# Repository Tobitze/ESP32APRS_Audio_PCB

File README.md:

This is a PCB for my APRS BLE TNC, which is based on the ESP32APRS_Audio Firmware from nakhonthai - see https://github.com/nakhonthai/ESP32APRS_Audio.
This PCB implements the basic components to work with an esp32s3 and an external handheld Radio, like filters and DC Offsets. The Radio is connected via the Kenwood Plug. This is not intended for an RF Module on the Board!
It's oriented around Nakhonthai's layouts with some small changes.
I designed it for my esp32s3-N16R8 (the one already on a PCB, not the chip itself). Please check your Pin configuration before using this.

TODO: This PCB has three UART Connectors, but no I2C für WX Sensors. You can reconfigure one of them, but the pin Layout then needs one wire on the pcb.

This PCB has:

-NPN transistor for PTT control

-GPIO PWM Filters (Audio Output)

-ADC Input DC Bias (Audio Input)

-UART Connectors for external GPS PCBs and other stuff (Supposed to be under the Board)

-Connectors for simple three-pin Sensors

-Every other Pin of the esp32 is led out to some connectors for future extensions, including four power pins

If you don't want to order this for yourself, get in touch; maybe I still have some lying around. (See qrz.com for email address)

73 de
DC4TA

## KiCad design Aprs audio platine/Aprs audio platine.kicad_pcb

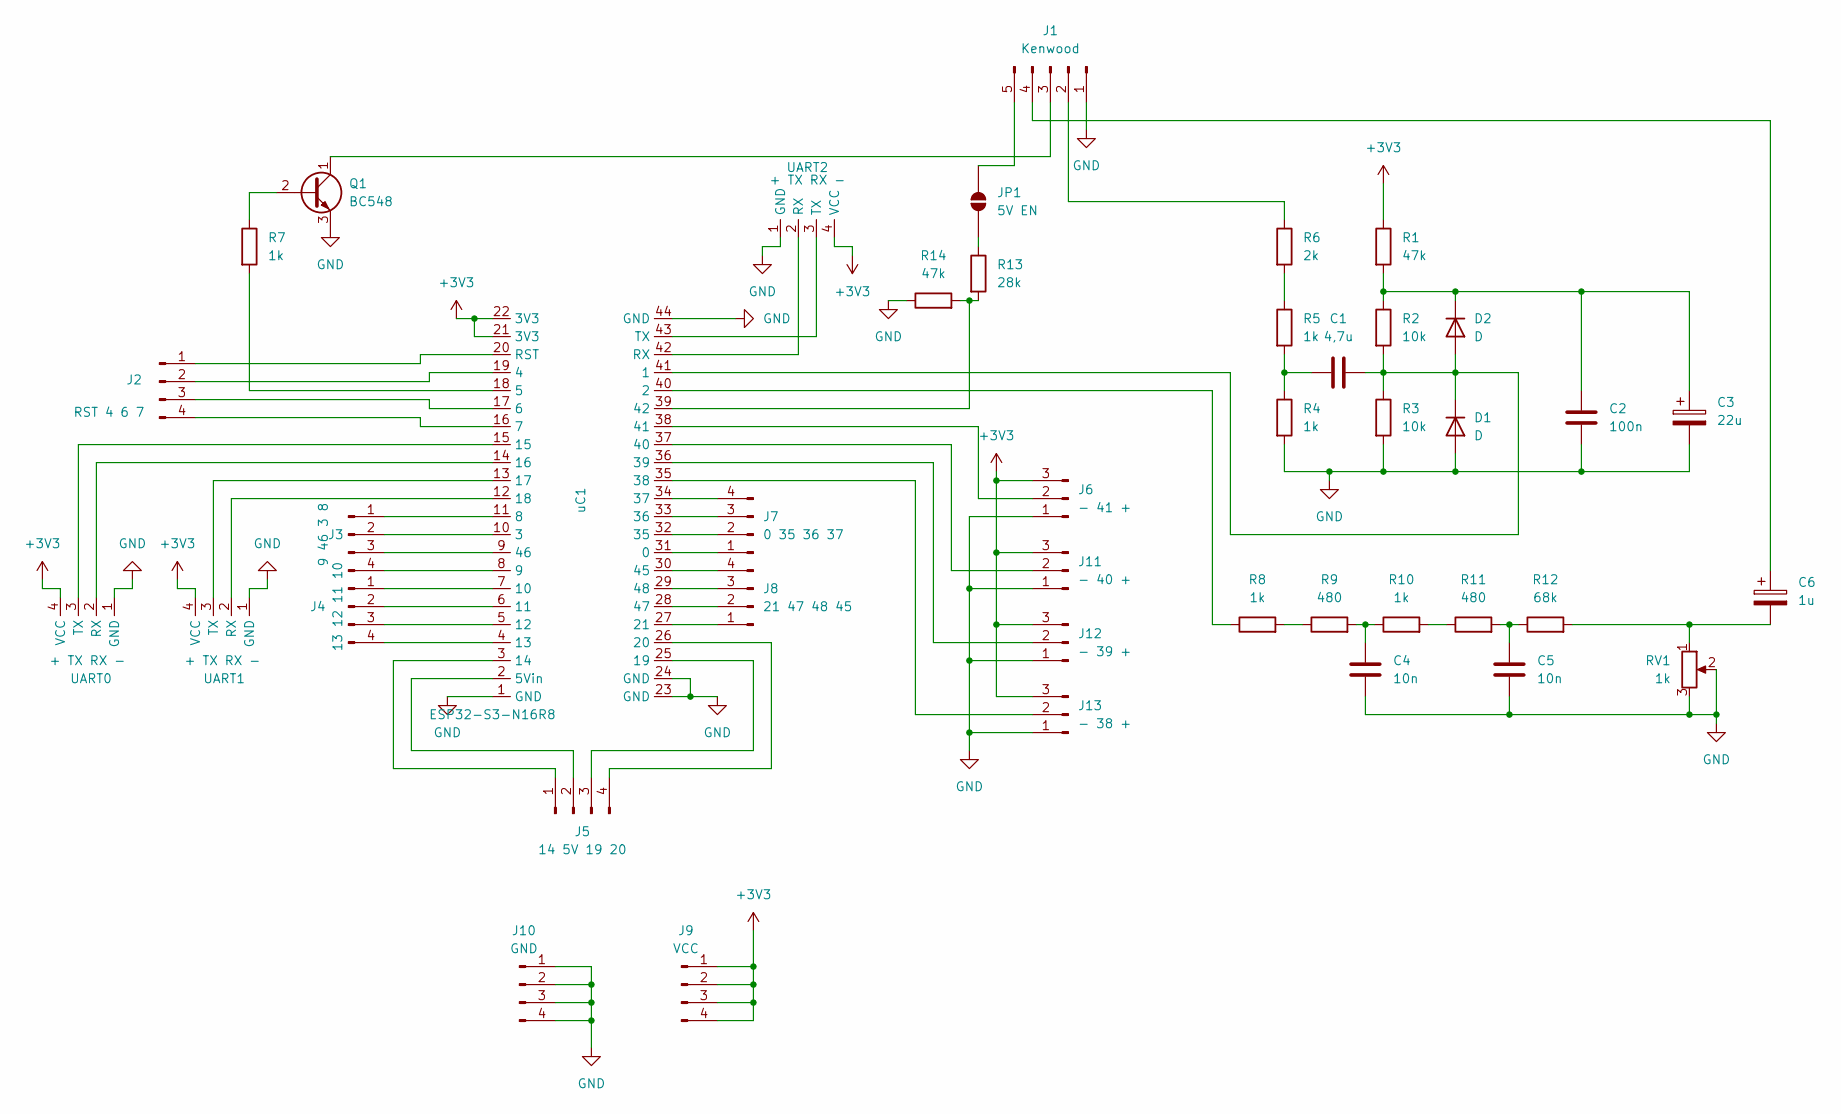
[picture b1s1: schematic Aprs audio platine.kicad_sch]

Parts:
C1: 4,7u; C_Disc_D3.0mm_W2.0mm_P2.50mm
C2: 100n; C_Disc_D3.0mm_W2.0mm_P2.50mm
C3: 22u; CP_Radial_D5.0mm_P2.50mm
C4, C5: 10n; C_Disc_D3.0mm_W2.0mm_P2.50mm
C6: 1u; CP_Radial_D5.0mm_P2.50mm
D1, D2: D; D_DO-34_SOD68_P7.62mm_Horizontal
J1: Kenwood; SolderWire-0.25sqmm_1x05_P4.2mm_D0.65mm_OD1.7mm
J2: RST 4 6 7; PinHeader_1x04_P2.54mm_Vertical
J3: 9 46 3 8; PinHeader_1x04_P2.54mm_Vertical
J4: 13 12 11 10; PinHeader_1x04_P2.54mm_Vertical
J5: 14 5V 19 20; PinHeader_1x04_P2.54mm_Vertical
J6: - 41 +; PinHeader_1x03_P2.54mm_Vertical
J7: 0 35 36 37; PinHeader_1x04_P2.54mm_Vertical
J8: 21 47 48 45; PinHeader_1x04_P2.54mm_Vertical
J9: VCC; PinHeader_1x04_P2.54mm_Vertical
J10: GND; PinHeader_1x04_P2.54mm_Vertical
J11: - 40 +; PinHeader_1x03_P2.54mm_Vertical
J12: - 39 +; PinHeader_1x03_P2.54mm_Vertical
J13: - 38 +; PinHeader_1x03_P2.54mm_Vertical
JP1: 5V EN; SolderJumper-2_P1.3mm_Open_RoundedPad1.0x1.5mm
Q1: BC548; TO-92_Inline
R1, R14: 47k; R_Axial_DIN0309_L9.0mm_D3.2mm_P12.70mm_Horizontal
R2, R3: 10k; R_Axial_DIN0309_L9.0mm_D3.2mm_P12.70mm_Horizontal
R4, R5, R7, R8, R10: 1k; R_Axial_DIN0309_L9.0mm_D3.2mm_P12.70mm_Horizontal
R6: 2k; R_Axial_DIN0309_L9.0mm_D3.2mm_P12.70mm_Horizontal
R9, R11: 480; R_Axial_DIN0309_L9.0mm_D3.2mm_P12.70mm_Horizontal
R12: 68k; R_Axial_DIN0309_L9.0mm_D3.2mm_P12.70mm_Horizontal
R13: 28k; R_Axial_DIN0309_L9.0mm_D3.2mm_P12.70mm_Horizontal
RV1: 1k; TerminalBlock_MetzConnect_Type055_RT01503HDWU_1x03_P5.00mm_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
UART0, UART1, UART2: + TX RX -; NEO-6M-Board
uC1: ESP32-S3-N16R8; esp32s3board

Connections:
+3V3: J6.3, J9.1, J9.2, J9.3, J9.4, J11.3, J12.3, J13.3, R1.1, UART0.4 (VCC), UART1.4 (VCC), UART2.4 (VCC), uC1.21 (3V3), uC1.22 (3V3)
GND: C2.2, C3.2, C4.2, C5.2, D1.2 (A), J1.1, J6.1, J10.1, J10.2, J10.3, J10.4, J11.1, J12.1, J13.1, Q1.3 (E), R3.2, R4.2, R14.1, RV1.2, RV1.3, UART0.1 (GND), UART1.1 (GND), UART2.1 (GND), uC1.1 (GND), uC1.23 (GND), uC1.24 (GND), uC1.44 (GND)
unnamed: C1.1, R4.1, R5.2
unnamed: C4.1, R9.2, R10.1
unnamed: C5.1, R11.2, R12.1
unnamed: C6.2, R12.2, RV1.1
unnamed: C1.2, D1.1 (K), D2.2 (A), R2.2, R3.1, uC1.41 (1)
unnamed: C2.1, C3.1, D2.1 (K), R1.2, R2.1
unnamed: J1.2, R6.1
unnamed: J1.3, Q1.1 (C)
unnamed: C6.1, J1.4
unnamed: J1.5, JP1.2 (B)
unnamed: J2.1, uC1.20 (RST)
unnamed: J2.2, uC1.19 (4)
unnamed: J2.3, uC1.17 (6)
unnamed: J2.4, uC1.16 (7)
unnamed: J3.1, uC1.11 (8)
unnamed: J3.2, uC1.10 (3)
unnamed: J3.3, uC1.9 (46)
unnamed: J3.4, uC1.8 (9)
unnamed: J4.1, uC1.7 (10)
unnamed: J4.2, uC1.6 (11)
unnamed: J4.3, uC1.5 (12)
unnamed: J4.4, uC1.4 (13)
unnamed: J5.1, uC1.3 (14)
unnamed: J5.2, uC1.2 (5Vin)
unnamed: J5.3, uC1.25 (19)
unnamed: J5.4, uC1.26 (20)
unnamed: J6.2, uC1.38 (41)
unnamed: J7.1, uC1.31 (0)
unnamed: J7.2, uC1.32 (35)
unnamed: J7.3, uC1.33 (36)
unnamed: J7.4, uC1.34 (37)
unnamed: J8.1, uC1.27 (21)
unnamed: J8.2, uC1.28 (47)
unnamed: J8.3, uC1.29 (48)
unnamed: J8.4, uC1.30 (45)
unnamed: J11.2, uC1.37 (40)
unnamed: J12.2, uC1.36 (39)
unnamed: J13.2, uC1.35 (38)
unnamed: JP1.1 (A), R13.1
unnamed: Q1.2 (B), R7.1
unnamed: R5.1, R6.2
unnamed: R8.2, R9.1
unnamed: R10.2, R11.1
unnamed: UART0.2 (RX), uC1.14 (16)
unnamed: UART0.3 (TX), uC1.15
unnamed: UART1.2 (RX), uC1.12 (18)
unnamed: UART1.3 (TX), uC1.13 (17)
unnamed: UART2.2 (RX), uC1.42 (RX)
unnamed: UART2.3 (TX), uC1.43 (TX)
unnamed: R8.1, uC1.40 (2)
unnamed: R7.2, uC1.18 (5)
unnamed: R13.2, R14.2, uC1.39 (42)

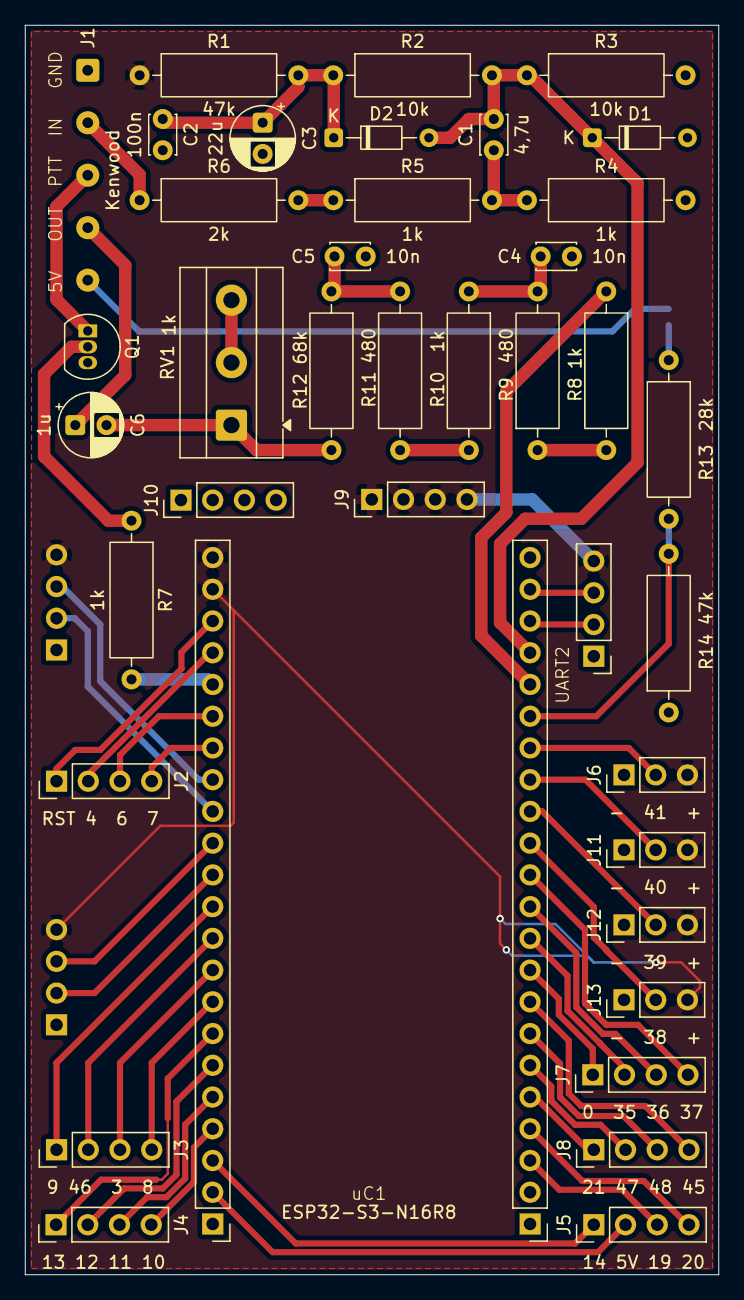
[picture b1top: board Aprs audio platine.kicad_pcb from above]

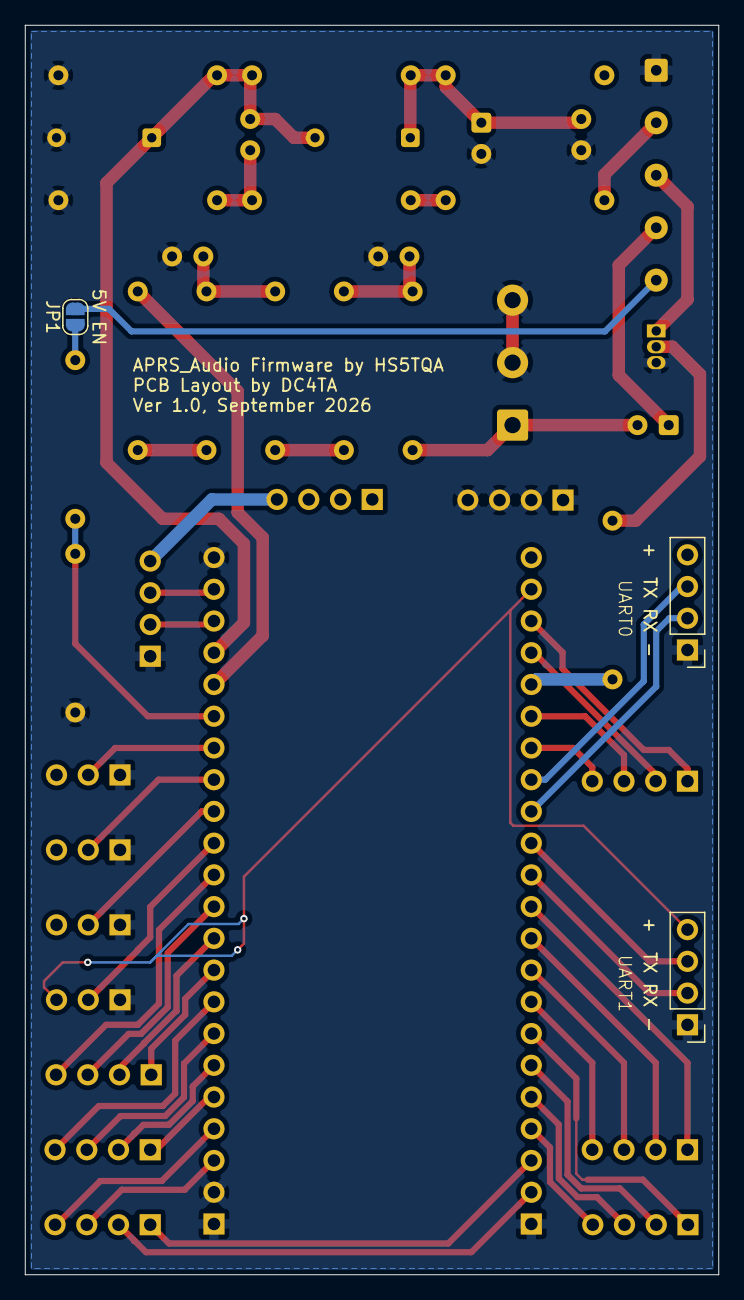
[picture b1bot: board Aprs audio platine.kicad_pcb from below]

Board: 2 copper layers, 55.5 x 100.0 mm, 42 parts (3 on the bottom side), 54 nets.
